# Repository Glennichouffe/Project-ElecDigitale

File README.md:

# Project-ElecDigitale
Repository pour le code Java et C, aussi pour les simulations et le fichier "Eagle" du projet en electronique digitale

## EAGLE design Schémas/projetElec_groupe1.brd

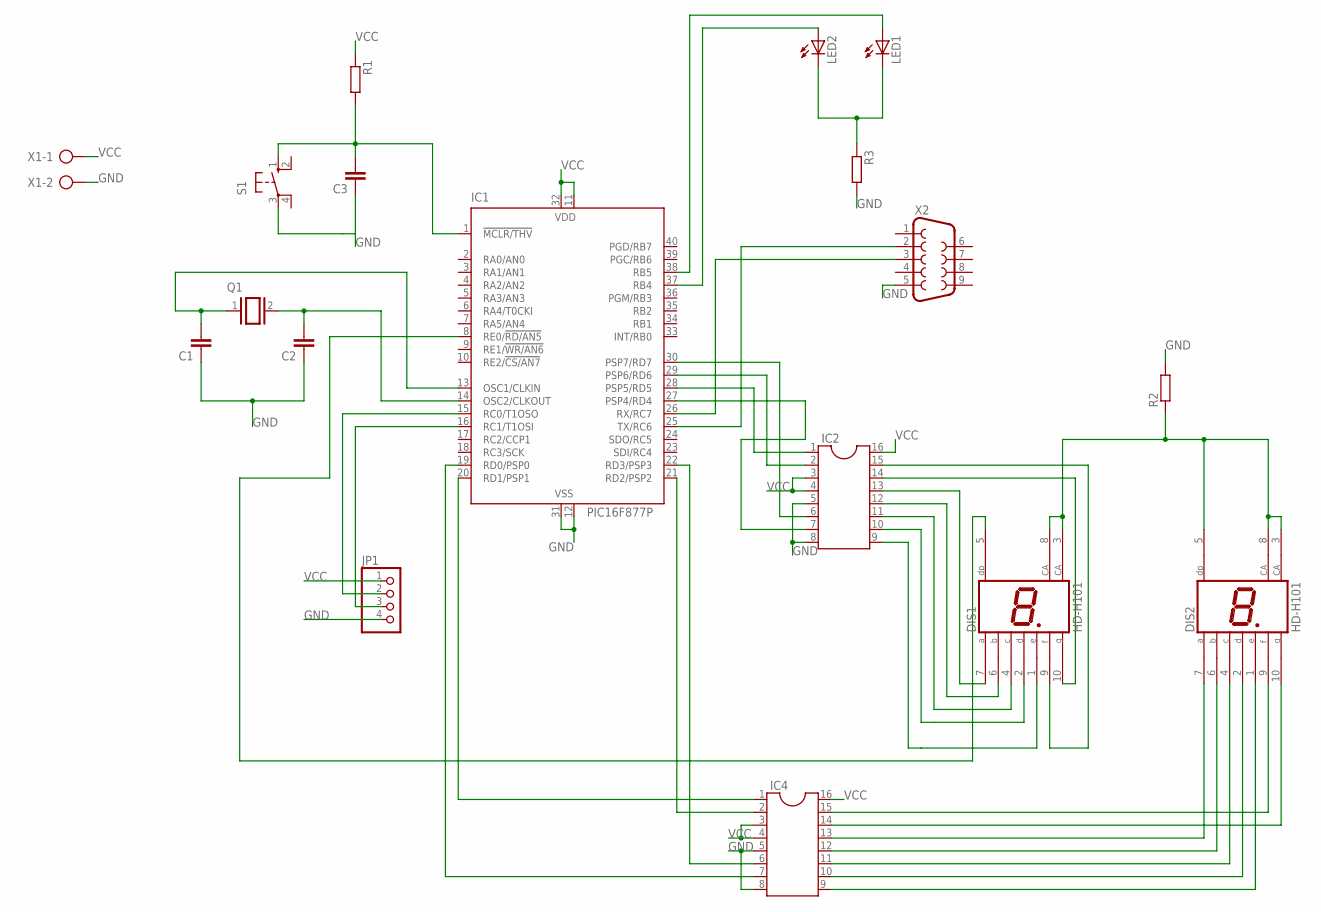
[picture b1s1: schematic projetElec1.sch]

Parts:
C1, C2, C3: C-EU025-030X050; C025-030X050
DIS1, DIS2: HD-H101; HDSP-M
IC1: PIC16F877P; DIL40
IC2, IC4: DIL16
JP1: PINHD-1X4; 1X04
LED1, LED2: LED5MM
Q1: XTAL/S; QS
R1, R2, R3: R-EU_0204/7; 0204/7
S1: 10-XX; B3F-10XX
X1: AK300/2
X2: F09H

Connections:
GND: C1.1, C2.1, C3.1, IC1.12 (VSS), IC1.31 (VSS), IC2.5, IC2.8, IC4.5, IC4.8, JP1.4, R2.2, R3.2, S1.3, X1.2, X2.5
unnamed: C1.2, IC1.13 (OSC1/CLKIN), Q1.1
unnamed: C2.2, IC1.14 (OSC2/CLKOUT), Q1.2
unnamed: C3.2, IC1.1 (!MCLR/THV), R1.2, S1.1 (S)
unnamed: IC1.38 (RB5), LED1.A
unnamed: LED1.K (C), LED2.K (C), R3.1
unnamed: IC1.37 (RB4), LED2.A
unnamed: IC1.15 (RC0/T1OSO), JP1.2
unnamed: IC1.16 (RC1/T1OSI), JP1.3
unnamed: DIS1.10 (G), IC2.14
unnamed: IC1.25 (TX/RC6), X2.2
unnamed: IC1.26 (RX/RC7), X2.3
unnamed: IC1.28 (PSP5/RD5), IC2.1
unnamed: IC1.29 (PSP6/RD6), IC2.2
unnamed: IC1.30 (PSP7/RD7), IC2.6
unnamed: DIS1.7 (A), IC2.13
unnamed: IC1.20 (RD1/PSP1), IC4.1
unnamed: IC1.27 (PSP4/RD4), IC2.7
unnamed: DIS1.6 (B), IC2.12
unnamed: DIS1.4 (C), IC2.11
unnamed: DIS1.2 (D), IC2.10
unnamed: DIS1.1 (E), IC2.9
unnamed: DIS1.5 (DP), IC1.8 (RE0/!RD/AN5)
unnamed: DIS2.3 (CA), DIS2.5 (DP), DIS2.8 (CA), R2.1
unnamed: DIS1.3 (CA), DIS1.8 (CA)
unnamed: DIS1.9 (F), IC2.15
unnamed: IC1.19 (RD0/PSP0), IC4.7
unnamed: IC1.21 (RD2/PSP2), IC4.2
unnamed: IC1.22 (RD3/PSP3), IC4.6
unnamed: DIS2.7 (A), IC4.13
unnamed: DIS2.6 (B), IC4.12
unnamed: DIS2.4 (C), IC4.11
unnamed: DIS2.2 (D), IC4.10
unnamed: DIS2.1 (E), IC4.9
unnamed: DIS2.10 (G), IC4.14
unnamed: DIS2.9 (F), IC4.15
VCC: IC1.11 (VDD), IC1.32 (VDD), IC2.3, IC2.4, IC2.16, IC4.3, IC4.4, IC4.16, JP1.1, R1.1, X1.1

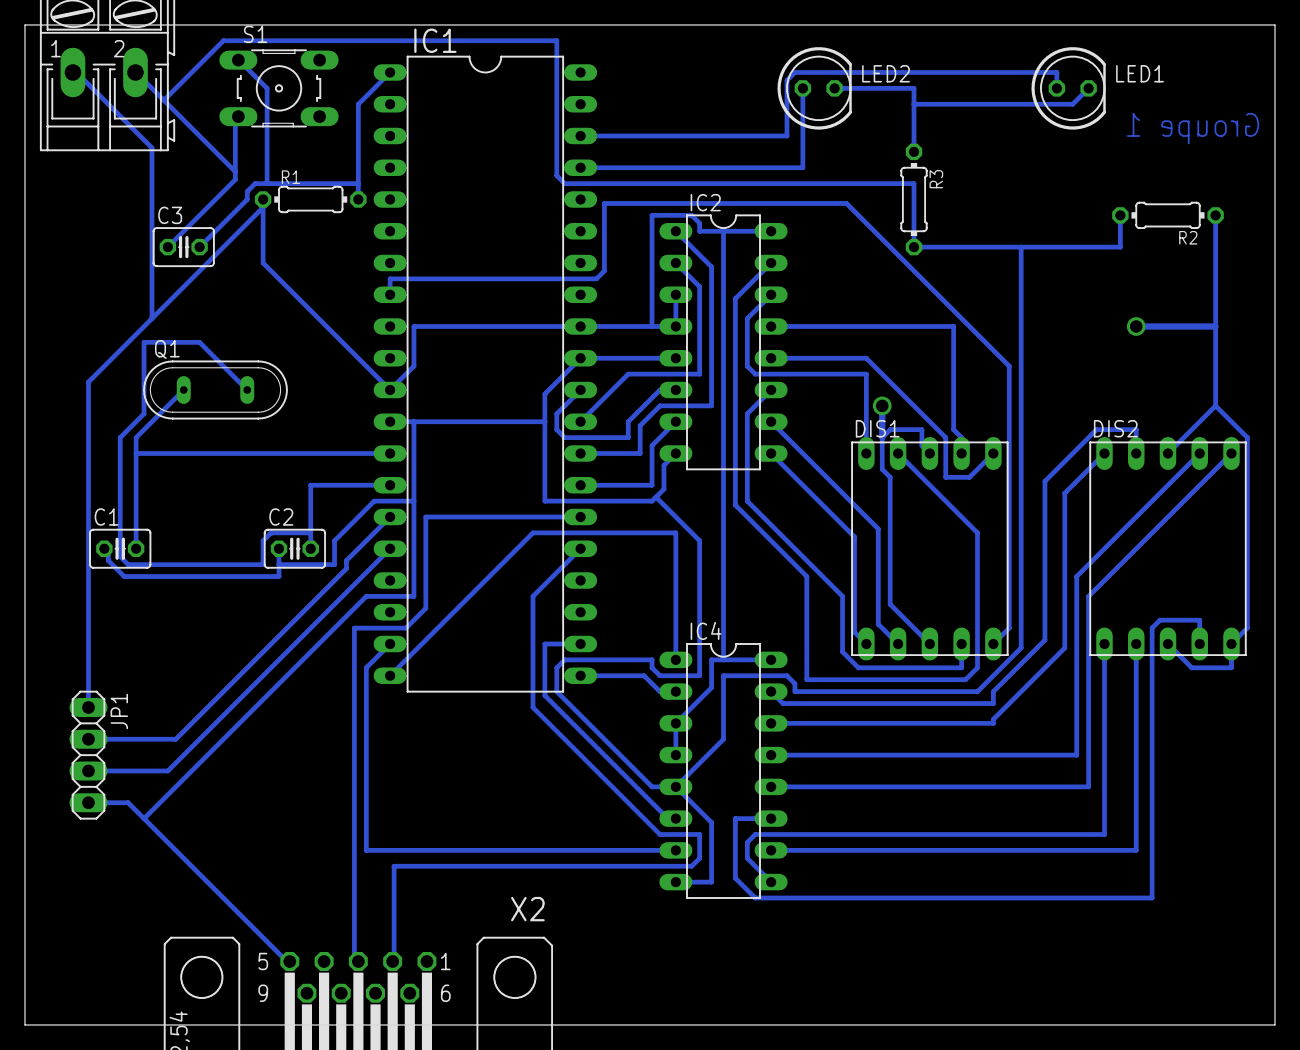
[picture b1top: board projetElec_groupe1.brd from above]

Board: 2 copper layers, 100.0 x 80.0 mm, 18 parts (0 on the bottom side), 37 nets.

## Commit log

2020-03-05 test bro
2020-03-05 Suppression du test
2020-05-10 Ajout d'une partie du code java
2020-05-10 Add Gui.Java
2020-05-10 Create projetElec.c
    Code C fonctionnelle
2020-05-10 ajout schemas
2020-05-10 chgmt valeur
